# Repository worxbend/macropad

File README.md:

# macropad

A 12-key macropad on its own 4-layer PCB. Two rotary encoders, an always-on memory display,
light bars in the case sides, one USB-C port. Board, case and firmware are all generated from
code in this repository and checked against one shared file, [`board.toml`](board.toml).

It is the small, PCB-based sibling of [macropad-nyxilab](https://github.com/worxbend/macropad-nyxilab):
90 x 90 mm instead of 159 x 98 mm, and no hand wiring.

*Top: a render of the case model, not a photo. Bottom: the firmware running in its simulator, not a
recording of a device. The display in the render shows the simulator's own picture.*

> **Status: design files only. Nothing has been built.**
> No board has been ordered. No case has been printed or milled. The firmware has never run on a chip.
> Every claim below is what the design files and their automatic checks say. Read
> [Before you order](#before-you-order) first.

## Contents

1. [Status](#status)
2. [What it is](#what-it-is)
3. [Gallery](#gallery)
4. [Build one](#build-one)
5. [Stock keymap](#stock-keymap)
6. [Work on the design](#work-on-the-design)
7. [What is checked](#what-is-checked)
8. [Where things are](#where-things-are)
9. [Before you order](#before-you-order)
10. [License](#license)

## Status

Checked on 2026-11-14 by running the commands in the last column on this repository.

| Part | State | How it was checked |
|---|---|---|
| Circuit | Done. 52 nets, 75 machine-placed parts, 1 left unpopulated (C13). | `make pcb-test`: netlist self-check, 37 unit tests pass |
| Schematic | Done. Generated KiCad 9 sheet. ERC: 0 errors, 0 warnings. | `make pcb-place` (report in `pcb/.build/erc.rpt`) |
| PCB layout | **Fully routed.** 827 tracks, 164 vias, 0 unrouted pads. DRC: 0 violations, 0 unconnected, 0 differences from the schematic. | `make pcb-check` |
| Order files | Written: 11 Gerbers, 2 drill files, a BOM and a placement file each for PCBWay and JLCPCB. They agree with the board and with each other. | `make pcb-fab`, `make pcb-test` |
| Case | Done. 659 part pairs per variant, 0 clashes. Every named clearance and measurement inside its limit. Printed and milled variant. | `make test` |
| Firmware | Builds. 248 tests pass. UF2 in `firmware/dist/`. | `make test`, `make firmware` |
| Real hardware | **None.** No board, no print, no flash. | - |

One accepted DRC warning remains: the USB-C footprint differs from its library copy, because its
silkscreen is cut at the board edge. It is named in `pcb/gen/build.py` and explained in
[pcb/README.md](pcb/README.md).

A clean DRC does not make a working board. The list of things a person still has to look at is in
[Before you order](#before-you-order).

## What it is

| | |
|---|---|
| MCU | RP2354A: the Pico 2 chip (RP2350) with 2 MB flash inside the package |
| Keys | 12 x MX, HanElectricity hot-swap sockets (Kailh CPG151101S11 compatible), one GPIO per key (no matrix, no diodes) |
| Knobs | 2 x Alps EC11E18244AU with push switch, 36 clicks per turn. 3.3 kΩ pull-ups on the A and B contacts give each contact 1 mA |
| Display | nice!view (Sharp memory LCD, 160 x 68, monochrome, readable in sunlight), soldered on a 5-pin male header |
| Light | 8 x SK6812 SIDE-A side-emitting RGB LEDs on the PCB edges, behind two light bars that show as a line in the gap round the case |
| USB | One USB-C port for power, data and flashing. ESD diodes, 500 mA resettable fuse |
| Debug | Six test pads on the bottom face: SWCLK, SWDIO, GND, 5V, 3V3, 1V1. BOOT and RESET buttons reached through the case floor |
| PCB | 84 x 82.5 mm, 4 layers, 1.6 mm. Every machine-placed part is on the bottom face, next to the ground plane on In2 |
| Case | Base and top with a lap joint and a shadow gap between them, flush lens over the display, 2 light bars, 2 knobs, 2 foot strips and a centre pad that hide the screws, optional 6° tilt bar. 3D-print or CNC variant. The aluminium case is bonded to GND at one screw (H1) |
| Size | 90.0 x 90.0 x 17.5 mm, 35.5 mm from the underside to the top of the knobs. The foot strips add 1.2 mm |
| Firmware | Rust ([embassy](https://embassy.dev)). 4 layers, macros, tap-hold keys, per-layer knob functions, animated display, reactive lighting |
| Host | Shows up as a USB keyboard plus media keys. No driver, no host software |

How the pieces connect:

```mermaid
flowchart LR
    usb[USB-C] -->|5 V through fuse| reg[AP2112K 3.3 V]
    usb <-->|D+ D- through ESD diodes| mcu[RP2354A]
    reg --> mcu
    keys[12 MX keys] -->|12 GPIO| mcu
    knobs[2 encoders with push] -->|6 GPIO| mcu
    mcu -->|SPI0| lcd[nice!view]
    mcu -->|GPIO9| shift[74LVC1T45 to 5 V]
    shift --> leds[8 x SK6812 SIDE-A]
    usb -->|5 V| leds
```

More detail: [docs/hardware.md](docs/hardware.md).

## Gallery

Every picture is generated by the code in this repository. None is a photo.

### Case

The case is a 90 mm square slab with one flat top face. The printed variant has R 7.0 arc corners; the
milled variant has continuous-curvature corners. The gap between the two shells runs all round, but it
lights only along two 46.5 mm stretches, one per side. The glow colour and the brightness in the
light-line picture are guesses: no optical simulation was done. The colours are proposals.
More views, the print orientation and the design notes: [cad/README.md](cad/README.md).

### PCB

The parts on the populated board are block models with nominal heights. They show where things
are. They are not the makers' 3D models.

Schematic as [PDF](docs/images/pcb/schematic.pdf). Copper layers:
[top](docs/images/pcb/copper-top.svg), [ground](docs/images/pcb/copper-ground.svg),
[power](docs/images/pcb/copper-power.svg), [bottom](docs/images/pcb/copper-bottom.svg).
Assembly drawings: [top](docs/images/pcb/assembly-top.svg), [bottom](docs/images/pcb/assembly-bottom.svg).
Routing notes and the full check list: [pcb/README.md](pcb/README.md).

### Display and lighting

The 8 LEDs over the demo session, one row per LED. Colours are brightened for the screen.
Screens, controls and timing: [firmware/README.md](firmware/README.md).

### Drawings

The sheets are in `cad/exports/drawings/` as SVG and PDF. Dimension texts are computed from the model.
The two CNC sheets carry part numbers, revision A, one finish (bead blast and clear anodise), ISO
2768-m with the critical fits toleranced, the M2 thread callouts, the anodise masks for the case
ground at S1, a USB opening detail and, on the base, the laser-mark note. `make cad` reads every exported STEP and STL back: one closed solid per part, no
free edges, volumes within 0.1 %.

## Build one

Nobody has done this yet. The guides are written from the design files. Expect to find mistakes,
and please report them.

The plan for the first prototype, step by step with a pass test for each, is
[docs/prototype.md](docs/prototype.md): measure the parts, order the board, print coupons and a case,
bring the board up, and only then pay for a milled case.

1. **Read [Before you order](#before-you-order).** Decide whether you accept the open points.
2. **Order the board.** [docs/ordering.md](docs/ordering.md): PCBWay step by step, 5 bare boards
   with 2 assembled on the bottom face, with the files in `pcb/fab/`. JLCPCB is the alternative on
   the same page. Buy the parts the board house does not place: [docs/parts.md](docs/parts.md).
3. **Make the case.** Print the coupons first, then the case. Mill it only after a printed case
   closes on measured parts. Orientation, settings and CNC notes are in
   [cad/README.md](cad/README.md#printing).
4. **Assemble.** [docs/assembly.md](docs/assembly.md): bring up the bare board from a current-limited
   supply, run the hardware test, solder the two encoders and the display, then close the case with
   six screws.
5. **Flash.** [docs/flashing.md](docs/flashing.md): hold BOOT, plug in, copy
   `firmware/dist/macropad.uf2` to the `RP2350` drive. The same page lists what to check first when
   something does not work.

To change what the keys do: [docs/keymap.md](docs/keymap.md).

## Stock keymap

Four layers. Tap the left knob for the next layer. The display always shows the active layer's labels.

| Layer | Keys, row by row | Left knob | Right knob | Right knob press |
|---|---|---|---|---|
| MEDIA | PREV PLAY NEXT STOP / F13 F14 F15 F16 / F17 F18 F19 F20 | Volume | Screen brightness | Mute |
| EDIT | UNDO REDO CUT COPY / PASTE ALL SAVE FIND / ESC TAB-or-Shift DEL LINE | Undo, redo | Cursor left, right | Enter |
| NAV | HOME UP END PGUP / LEFT DOWN RIGHT PGDN / TAB- TAB+ BACK FWD | Up, down arrow | Previous, next tab | Enter |
| NUM | 7 8 9 BKSP / 4 5 6 ENTER / 1 2 3 0 | Volume | Minus, plus | Period |

| Gesture | Does |
|---|---|
| Hold the left knob + a top-row key | Jump to layer 1, 2, 3 or 4 |
| Hold the left knob + turn the right knob | LED brightness, 8 steps down to off |
| Hold both knobs for 1 s | Restart as a USB drive for a new firmware file |

## Work on the design

### Tools

| For | You need |
|---|---|
| Firmware | Rust (stable) with `rustup target add thumbv8m.main-none-eabihf`, Python 3.11 or newer, `make` |
| Simulator pictures | The above plus ImageMagick (`magick`) |
| Case | Python 3.12 and a virtual environment in `cad/.venv` (set-up in [cad/README.md](cad/README.md#build)). `rsvg-convert` for the PDF and PNG drawings |
| PCB | Docker. All KiCad work runs in the pinned image `kicad/kicad:9.0.9` through `pcb/kicad.sh` |

### Commands

Run `make help` for this list.

| Command | Does | Needs | Time |
|---|---|---|---|
| `make test` | Everything that can be checked without Docker or hardware | Rust, `cad/.venv` | about 3 minutes |
| `make firmware` | Tests, lints, board and HID checks, `firmware/dist/macropad.uf2` | Rust | under 1 minute |
| `make ui-images` | Redraws `docs/images/ui/` and the demo GIF from the simulator | Rust, ImageMagick | about 1 minute |
| `make cad` | Case self-test, checks, STEP/STL exports, renders, drawings | `cad/.venv` | about 3 minutes |
| `make pcb` | `pcb-place`, `pcb-check`, `pcb-fab` in order | Docker | about 2 minutes |
| `make pcb-place` | Schematic, placed and routed board, 3D models, pictures | Docker | about 1 minute |
| `make pcb-check` | KiCad design-rule check, board against schematic | Docker | seconds |
| `make pcb-fab` | Gerbers, drill files, BOM, placement list into `pcb/fab/` | Docker | seconds |
| `make pcb-test` | Netlist self-check and the PCB generator's unit tests | Python | seconds |
| `make docs-check` | Every file and picture named in a Markdown file exists | Python | seconds |

### One file drives three builds

`board.toml` holds the positions and the GPIO numbers. The PCB generator, the case model and the
firmware's board check all read it.

1. Change a position or a pin in `board.toml`.
2. Run `make pcb cad firmware`.
3. If parts or pins moved on the PCB, the routing order may need a new search:
   `pcb/kicad.sh python3 pcb/gen/build.py order` (about 10 minutes; it can fail).

Nothing in `pcb/kicad/` is drawn by hand. Hand edits are lost on the next `make pcb-place`.
Change `pcb/gen/circuit.py` or `pcb/gen/route.py` instead.

## What is checked

No check here replaces a prototype. They catch the mistakes a computer can catch.

| Area | Check | Result on 2026-11-14 |
|---|---|---|
| PCB | Netlist self-check in `circuit.py` | 52 nets, passes |
| PCB | Router, schematic-writer and order-file unit tests (15, 19, 3) | 37 pass |
| PCB | `circuit.py` pins against KiCad's own RP2354A, regulator, ESD and level-shifter symbols | match |
| PCB | Schematic ERC, every severity | 0 errors, 0 warnings |
| PCB | DRC with board-against-schematic compare | 0 violations, 0 unconnected, 0 parity issues |
| PCB | Length limits on the USB pair, crystal and regulator nets; no via on the sensitive ones | pass (D+ 14.93 mm, D- 14.08 mm) |
| PCB | Order files agree: Gerbers newer than the board, one drill hit per via, both BOMs = both placement files = circuit, C13 in none of them | 75 parts, 1 do-not-populate, pass |
| PCB | Committed order files belong to the committed board: board hash, `unrouted pads 0` | pass |
| PCB | Case ground ring at H1 on GND and bare; encoder pull-ups beside their pins; no solder paste within 0.15 mm of a via hole; the design rules reach KiCad's DRC | pass |
| Case | Self-test: the measuring checks must catch 33 known-bad and sound shapes | 33 of 33 |
| Case | Interference, every part against every other, both variants | 659 pairs each, 0 clashes |
| Case | Every part one sound solid; wall thickness, screw bosses, light bar retention and insertion, lap joint, lens seat and stiffness, key and knob travel, knob seat on its shaft, square outline, corner curvature, frame swell, foot bearing, shell seat, text strokes, USB symmetry | all inside limits |
| Case | CNC: 3 mm tool reaches every pocket within 3 diameters, no sharp internal corner, no undercut beyond the USB opening's rounds | pass |
| Case | Exports read back: 11 STEP files, each part file one closed valid solid and the assembly 81, 0 free edges, volume within 0.1 % of the model and of its STL; no sliver faces in the CNC parts; 9 print coupons, each one watertight body | 11 of 11 STEP, 9 of 9 coupons |
| Case | Print: layer-by-layer bridge and overhang check for every printed part, faces on the 0.2 mm layer grid, show faces of the top at 45° or less, engraving on the bed 0.7 mm wide | pass |
| Firmware | Unit tests: `core` 192, `sim` 38, `uf2` 18 | 248 pass |
| Firmware | `tools/check_pins.py`: GPIOs, knob type, knob debounce longer than the encoder's 3 ms chatter, key grid, LED and simulator positions against `board.toml` | match |
| Firmware | `tools/check_hid.py`: the USB report descriptors, parsed as a host would | match |
| Firmware | UF2 converter refuses an image the chip could not boot | current image passes |
| Docs | `make docs-check`: files and pictures named in Markdown exist | pass |

CI ([`.github/workflows/ci.yml`](.github/workflows/ci.yml)) runs the checks that need neither Docker
nor a long case build: `make pcb-test`, `make docs-check` and the firmware tests with both board
checks. The workflow has not run on GitHub yet.

## Where things are

| Path | What |
|---|---|
| [`board.toml`](board.toml) | Positions and GPIOs. The single source of truth for PCB, case and firmware. |
| [`pcb/`](pcb/README.md) | The board. `gen/` is the generator (`circuit.py` is the circuit), `kicad/` the generated KiCad 9 project, `fab/` the order files, `lib/` footprints and block models. |
| [`cad/`](cad/README.md) | Parametric case (build123d). `macropad_case/` is the model and its checks, `exports/` holds STEP, STL, drawings and `checks.json`. |
| [`firmware/`](firmware/README.md) | Rust workspace: `core` logic, `fw` binary, `sim` simulator, `uf2` converter. `dist/macropad.uf2` is the built image. [`KEYMAP.md`](firmware/KEYMAP.md) is the keymap reference. |
| `tools/` | `check_pins.py` and `check_hid.py`: firmware against `board.toml` and against the HID rules. |
| [`docs/hardware.md`](docs/hardware.md) | Circuit in words, pin map, layer stack, test pads, mechanical stack. |
| [`docs/parts.md`](docs/parts.md) | Every part, its JLCPCB number, what to buy elsewhere, substitutions, a shopping list for the prototype. |
| [`docs/prototype.md`](docs/prototype.md) | The staged plan for the first prototype, with a pass test per step. |
| [`docs/ordering.md`](docs/ordering.md) | Ordering the assembled board from PCBWay, step by step; JLCPCB as the alternative. |
| [`docs/assembly.md`](docs/assembly.md) | Bring-up of a bare board, soldering, case assembly. |
| [`docs/flashing.md`](docs/flashing.md) | First flash, updates, troubleshooting. |
| [`docs/keymap.md`](docs/keymap.md) | Changing what the keys, knobs and lights do. |
| `docs/images/` | Generated pictures: `cad/`, `pcb/`, `ui/`. |

## Before you order

These are open. None is hidden by a green check.

**Electrical**

- **Crystal.** Raspberry Pi's reference part, the Abracon ABM8-272-T3, with the reference 15 pF
  capacitors and 1 kΩ. Not measured. If USB does not enumerate, look here first.
  See [docs/parts.md](docs/parts.md).
- **USB pair.** Two short tracks, 14.9 and 14.1 mm, not a tuned differential pair. No impedance was
  calculated. Normal for full-speed USB over this length; nobody measured it.
- **Regulator inductor dot.** The two papers disagree. Raspberry Pi's datasheet and reference
  layout put the dot on +1V1; Abracon's drawing labels the dot "+". The board follows Raspberry Pi:
  dot on the +1V1 pad, next to the silkscreen dot. Mounting on the bottom face changes nothing here:
  the regulator reads as Raspberry Pi's Fig. 26 seen from the bottom. Not verified on a part.
- **Placement rotations.** `pcb/fab/centroid-pcbway.csv` and `pcb/fab/cpl-jlcpcb.csv` carry KiCad's
  angles, also for the bottom-side parts. Whether the assembler wants those or (180 - r) is not
  settled. Check every part in their placement photos or preview before you pay;
  [docs/ordering.md](docs/ordering.md) has the checklist.
- **Suspend current.** The 8 LEDs draw about 4.8 mA even when dark, over the 2.5 mA a suspended USB
  device may draw, and the MCU keeps running too. Accepted for the prototype. The fix is a load
  switch on the LED supply: a board change.
- **C13 is left unpopulated.** Its 4.7 µF would double the 1.1 V regulator's output capacitor.
  The footprint stays; its two pads get solder paste and no part.
- **Hot-swap socket footprint.** The board uses HanElectricity's CPG151101S11-2. The footprint was
  drawn from Kailh's CPG151101S11 dimensions. HanElectricity's drawing gives the same main sizes, but
  nobody has checked the footprint against it pad by pad.

Settled since the last revision: the nice!view header order (MOSI, SCK, VCC, GND, CS) matches the
pinout on nicekeyboards.com, and the SK6812 SIDE-A pad order matches the OPSCO datasheet by function.
Both stay tagged `MEASURE` until someone checks a real module and LED.

**Mechanical**

- **`MEASURE` dimensions.** The nice!view's pixel window, its height on a plain male header (glass 4.4 mm
  above the PCB) and its header position, and the encoder heights (shaft end 24.5 mm, from the Alps
  drawing), come from drawings and community footprints, not from a caliper. The full table is in
  [cad/README.md](cad/README.md#assumptions-to-measure). Measure before you order the board:
  `display.header_x` moves J2 on the PCB.
- **Fits are guesses.** Lap joint 0.2 mm, deepest unsupported ledge 1.5 mm, sag of a printed bridge
  0.2 mm, printed screw holes 0.15 mm small, lens 1.0 mm cover glass on 0.13 mm tape. Print the nine
  coupons in `cad/exports/print/coupons/`, then one case, and measure before paying for machining.
- **The light line is a guess.** The LEDs shine into a bar that shows only through a 1.4 mm slit in the
  gap. How bright and how even that is has not been simulated or tried.
- **The top prints standing on its side wall**, 10.6 times taller than its footprint is wide. Tipping
  and warping are not modelled.

**Firmware**

- **Display orientation, knob direction, LED colour order** are one-line settings and are guesses
  until a board exists. [docs/flashing.md](docs/flashing.md) says where each one is.
- **USB IDs** are the pid.codes test pair `1209:0001`. Get your own before you give boards to others.
- Settings are not stored: brightness and layer reset at power-on.

**Review**

- The schematic and the layout are generated and machine-checked. No engineer has reviewed them.

## License

No license file yet. Until one is added, nobody else has the right to reuse this.
The side-LED footprint comes from another project under the MIT License; see `pcb/lib/SOURCES.txt`.

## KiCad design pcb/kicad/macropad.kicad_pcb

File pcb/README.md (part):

# PCB

The board is generated. Nothing in `pcb/kicad/` is drawn by hand: `make pcb-place` writes the
schematic, the placed and routed board, and the pictures in `docs/images/pcb/` from two inputs,
`board.toml` (positions, GPIOs) and `pcb/gen/circuit.py` (parts and nets).

**Not built.** No board has been ordered, assembled or powered. Everything below is what the design
files say and what the automatic checks confirm, nothing more.

Bare-board renders (KiCad 9). Left: top face with the keys, knobs and display header. Right: bottom
face with every machine-placed part.

The same board with its parts. The parts are block models: boxes and cylinders that `gen/models.py`
draws from each footprint's outline, with nominal heights. They show where things are and which face
they are on. They are not the manufacturers' models. Straight-on views:
[top](../docs/images/pcb/assembled-top.png), [bottom](../docs/images/pcb/assembled-bottom.png).

## Commands

| Command | What it does |
|---|---|
| `make pcb-place` | Place, route, pour, write the schematic, check it, export the pictures. About 2 minutes. Fails when a pad is left unrouted, after writing `routing.txt`. |
| `make pcb-check` | KiCad design-rule check of the routed board. Fails on any error or unconnected item. |
| `make pcb-fab` | Gerbers, drill files, JLCPCB and PCBWay BOMs and placement files into `pcb/fab/`, then a check that they agree. |
| `make pcb-test` | `python3 -m unittest discover -s pcb/gen -p 'test_*.py'`: router, schematic-writer and order-file tests (37). Plain Python, no KiCad needed. CI runs it. |
| `pcb/kicad.sh python3 pcb/gen/build.py order` | Search for a routing order again. Needed after moving parts or pins. About 10 minutes. |

All KiCad work runs in the pinned container `kicad/kicad:9.0.9` through `pcb/kicad.sh`.

## Files

| Path | What |
|---|---|
| `gen/circuit.py` | The circuit: every part, its JLCPCB number, position, rotation, nets and do-not-populate mark. Pure Python. |
| `gen/layout.py` | Footprints, board outline, planes, design rules (also written into `kicad/macropad.kicad_pro`), the MCU footprint's paste windows, placement self-checks. |
| `gen/router.py` | Two-layer grid router. Pure Python, tested in `gen/test_router.py`. |
| `gen/route.py` | The routing plan: what is routed in which order, and the hand-placed vias. |
| `gen/route_order.txt` | MCU nets that are routed before the others. Written by `build.py order`. |
| `gen/silk.py` | Silkscreen text. |
| `gen/models.py` | Block 3D models of the parts, written to `lib/3d/`. |
| `gen/schematic.py` | Writes the KiCad schematic from `circuit.py`, with KiCad's library symbols. |
| `gen/sheet_layout.py` | Where each part sits on the schematic sheet and which wires are drawn. Data only. |
| `gen/symlib.py`, `gen/sexpr.py` | Read KiCad symbol libraries; draw the two symbols KiCad has none for. |
| `gen/test_schematic.py` | Tests of the schematic writer. |
| `gen/test_order_files.py` | The committed board and order files belong together: no unrouted pad, Gerbers not older than the board, board hash as `make pcb-fab` recorded it. |
| `gen/fab.py` | JLCPCB and PCBWay BOMs, JLCPCB placement list, PCBWay centroid file, and their checks. |
| `kicad/` | Generated KiCad 9 project: board, schematic, symbol library, library tables. |
| `routing.txt` | Generated report: track length and via count per net. |
| `netlist.txt` | Generated netlist: `python3 pcb/gen/circuit.py > pcb/netlist.txt`. |
| `lib/` | The project footprints and where they come from (`lib/SOURCES.txt`). The MCU footprint with windowed exposed-pad paste is generated by `gen/layout.py`. `lib/3d/` holds the generated block models. |
| `fab/` | Generated order files: `macropad-gerbers.zip`, `bom-jlcpcb.csv`, `cpl-jlcpcb.csv`, `bom-pcbway.csv`, `centroid-pcbway.csv`, and `board-sha256.txt` (the board they were made from). |

## Schematic

`kicad/macropad.kicad_sch` opens in KiCad 9. One A3 sheet, thirteen blocks.
[PDF](../docs/images/pcb/schematic.pdf), [SVG](../docs/images/pcb/schematic.svg).

It is a drawing of `circuit.py`, not a second source of truth:

- **Symbols come from KiCad's own libraries** (`Device:R`, `MCU_RaspberryPi:RP2354A`,
  `Regulator_Linear:AP2112K-3.3`, `Power_Protection:USBLC6-2SC6`, `Logic_LevelTranslator:SN74LVC1T45DBV`,
  `Connector:USB_C_Receptacle_USB2.0_16P` and so on). Pin numbers, pin names and pin types are
  therefore KiCad's, not typed here. Two parts have no KiCad symbol and are drawn as boxes: the
  side LED and the display header.
- **`sheet_layout.py` places the parts and lists the drawn wires.** Every other pin gets its supply
  symbol or its net label by rule. A drawn wire names its net, and the build refuses a wire that
  touches a pin of another net.

Checks on every `make pcb-place`:

1. `circuit.py` against KiCad's RP2354A symbol: each GPIO on its pin, each supply pin on its rail,
   the five pins of the flash inside the package open. Each chip's footprint against the footprint
   KiCad's symbol names.
2. `kicad-cli sch erc` at every severity: no error, no warning. That includes KiCad comparing each
   symbol on the sheet with its library.
3. KiCad exports the schematic's netlist; every pin's net is compared with `circuit.py`.
4. `kicad-cli pcb drc --schematic-parity`: every footprint, value and pad net on the board equals
   the schematic.

What this does not prove: KiCad's RP2354A symbol is itself someone's reading of the datasheet. It
is an independent one, and it agrees with `circuit.py` on all 61 pins. The SK6812 SIDE-A and
nice!view pin orders are still `MEASURE` items; no library covers them.

## Layers

| Layer | Use |
|---|---|
| F.Cu | Signals that cross the chip area, ground pour, the bare case ground ring at H1 |
| In1.Cu | 5 V plane. Inside it a 3.3 V island under the MCU, the display header and the USB pair, with a tongue out to the left encoder's pull-ups. Inside that a 1.1 V island under the chip |
| In2.Cu | Ground plane, unbroken except under the regulator inductor and the VREG_LX track |
| B.Cu | All machine-placed parts, most signals (1067 of 1308 mm of track), ground pour |

Drawings of each layer: [top](../docs/images/pcb/copper-top.svg),
[ground](../docs/images/pcb/copper-ground.svg), [power](../docs/images/pcb/copper-power.svg),
[bottom](../docs/images/pcb/copper-bottom.svg). Assembly drawings:
[top](../docs/images/pcb/assembly-top.svg), [bottom, mirrored](../docs/images/pcb/assembly-bottom.svg).

## Design rules

| Rule | Value | Note |
|---|---|---|
| Track width | 0.15 mm signals, 0.3 mm supply where it fits | |
| Clearance | 0.15 mm | The router keeps 0.17 mm to allow for its 0.1 mm grid |
| Via | 0.6 mm pad, 0.3 mm drill | No vias in pads, except four in the MCU's exposed pad. Every via is tented on the top face; on the bottom face all are tented except those four, which sit in the pad's mask opening and get no paste |
| Copper to board edge | 0.3 mm | |
| Copper to hole | 0.2 mm | Hole to hole 0.25 mm |
| Paste to via hole | 0.15 mm | No solder-paste aperture comes closer than this to a drilled via hole |

These are inside JLCPCB's published 4-layer limits as the previous author recorded them in
`layout.py`. PCBWay's capability page (read 2026-11-14) gives 0.1 mm track and space, 0.15 mm
minimum drill and 0.15 mm minimum via annular ring for its standard boards; the 0.6 / 0.3 mm via
has exactly 0.15 mm. Check them against the board house's page on the day you order.

KiCad 9 keeps the design rules in `kicad/macropad.kicad_pro`, not in the board file, and saving the
board from Python does not write that file. Until this change the file was the one written on
12 November and never touched by the build; its values happened to match. Now `make pcb-place`
writes `layout.DRC_RULES` and the default net class into it, and proves that `kicad-cli pcb drc`
reads them: a copy of the board with a project file that asks for 0.2 mm minimum track width must
fail on track width (199 findings on this board).

**Exposed-pad paste.** The MCU's exposed pad carries four 0.3 mm ground vias. KiCad's stock QFN-60
prints paste over them, so solder would wick into the holes. The board uses a project copy of the
stock footprint (`lib/macropad.pretty/QFN-60-1EP_7x7mm_P0.4mm_EP3.4x3.4mm_ViaWindows`, written by
`layout.py`) with the copper unchanged and the paste as nine windows: a 1.1 mm square in the middle,
four 0.95 x 1.1 mm arms between the vias and four 0.33 mm corner squares. They cover 50 % of the
pad and stay 0.15 mm clear of each via's 0.6 mm copper ring (0.3 mm from the hole). The vias are
tented on the top face. Nobody has checked the result with X-ray or a cut board; the corner squares
are small for a 0.12 mm stencil (area ratio about 0.69; the stencil thickness is a guess, ask the
board house).

## How the routing works

There is no autorouter program. `router.py` is a small grid router and `route.py` tells it what to
do, in this order:

1. **Four ground vias** in the MCU's exposed pad, between its paste windows.
2. **1.1 V regulator**, in Raspberry Pi's RP2350A Minimal pattern (RP2350 datasheet 6.3.8), mirrored
   for the bottom face. CIN (C11) sits across VREG_VIN (pin 49) and PGND (pin 47), COUT (C12) right
   behind it; their ground pads are joined and share two hand-placed vias. VREG_LX runs from pin 48
   between the pads of both capacitors to the inductor beyond them. VREG_FB runs from pin 50 to
   COUT. A 0.3 mm link takes the output from the inductor's +1V1 pad over the chip on the top layer
   into the 1.1 V island. Rule areas keep copper off the top and both inner layers under the
   inductor and the VREG_LX node, and keep the bottom ground pour out from between the inductor's
   pads. The VREG_LX rule areas are drawn after routing, round pin 48 and each routed VREG_LX segment
   with 0.2 mm to spare, so they follow the track wherever the router put it. Then USB D+ and D-, which squeeze past the regulator to their series resistors.
3. **MCU supply pins.** Each pin runs to its own 100 nF capacitor. The supply via sits between the
   pin and the capacitor, the ground via behind the capacitor, all on one line pointing away from
   the chip. These vias are placed by hand-computed geometry (`circuit.py`: `DECOUPLING_DISTANCE`,
   `SUPPLY_VIA_DISTANCE`, `GROUND_VIA_DISTANCE`), so they stay out of the lanes the neighbouring
   signal pins need.
4. **Crystal ground vias**, then **RUN**, then **SWCLK and SWDIO** out of the chip.
5. **Sensitive nets**, while the board is still empty: the USB lines from the connector, the crystal
   nets, VREG_AVDD. Then QSPI_SS, BOOT and VBUS.
6. **One via to the plane** for every remaining supply and ground pad.
7. **MCU signals**, one pin at a time: first a track out of the 16 mm square around the chip, then
   the rest of the net. Pins next to a capacitor go first. `route_order.txt` moves some nets to the
   front.
8. **Everything else**, shortest net first.

The router has no rip-up. When a net ends up walled in, `build.py order` routes the whole board
again with that net moved to the front, until every net connects. The order it finds is stored in
`route_order.txt`, so `make pcb-place` is one deterministic pass.

## Checks

| Check | Where | Fails the build |
|---|---|---|
| Every net has at least two pads | `circuit.py` | yes |
| Flips and rotations: MCU pins, hot-swap sockets, USB mouth, LED direction, capacitor orientation, crystal near XIN, fiducials on the assembly face | `layout.py:check_placement` | yes |
| Router: clearance to pads, tracks, vias, holes and the edge; vias; fan-out; escapes; determinism (15 tests) | `test_router.py` | yes, in `make pcb-test` and CI |
| Hand-placed vias have room | `router.py:add_via` | yes |
| Every net connects through tracks, vias and inner planes alone, before the outer ground pours are added | `build.py` | yes |
| Length limits: VREG_LX, USB_DM, USB_DP, XIN, XOUT, VREG_AVDD, VREG_FB to COUT; USB pair mismatch under 2 mm; no via on VREG_LX, on USB D+ from connector to chip, or on D- after its resistor; VREG_AVDD at least 0.75 mm from VREG_LX | `route.py:check_sensitive_lengths` | yes |
| No via and no top-layer track under the regulator inductor or the VREG_LX track | `route.py:check_regulator_keepout` | yes |
| No filled pour on the top or inner layers under the VREG_LX tracks, pin 48 or the inductor's pads, read back from the filled board | `route.py:check_no_pour_under_regulator` | yes |
| L1's polarity dot on B.SilkS and B.Fab sits at its +1V1 pad | `layout.py:check_placement` | yes |
| Encoder pull-ups R10-R13: on the bottom face, within 3 mm of their encoder pin, signal pad toward the pin | `layout.py:check_placement` | yes |
| Case ground ring at H1: on GND, at `mounting.ground_bond_hole`, `mounting.ground_bond_pad_diameter` wide, 2.2 mm hole, bare on the top face; no pad, track or via of another net within 0.15 mm | `layout.py:check_ground_bond`, after placement and after routing | yes |
| The MCU footprint's copy has exactly the stock footprint's copper pads; its paste windows stay inside the exposed pad, 0.15 mm clear of each via's copper ring, and cover 50 to 70 % of the pad | `layout.py:check_derived_footprints`, `check_paste_windows` | yes |
| Board-wide: no paste aperture within 0.15 mm of a via hole; every via tented on the top face | `layout.py:check_paste_clear_of_vias` | yes |
| `kicad-cli pcb drc` reads the rules from `macropad.kicad_pro`: a stricter project file must make it fail | `build.py:_check_rules_reach_drc` | yes |
| No pad left unrouted; `routing.txt` is written first | `build.py:place` | yes |
| Silkscreen: every visible text, footprint references included, at least 1.0 mm high with a 0.15 mm stroke; every stroked line at least 0.15 mm wide (the generator widens the stock footprints' 0.12 mm lines) | `silk.py:check_minimums` | yes |
| Every real part has a JLCPCB number, a manufacturer and a manufacturer part number | `circuit.py:check_sourcing` | yes, in `make pcb-test` |
| KiCad DRC at every severity: no warning either (loose track end, silkscreen over a pad or the edge). One named exception: J1 differs from its library copy, because its silkscreen is cut at the board edge | `build.py:_check_no_warnings` | yes |
| Every real part has a 3D model; no bottom-side model is taller than the gap to the case floor | `layout.py:write_models` | yes |
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
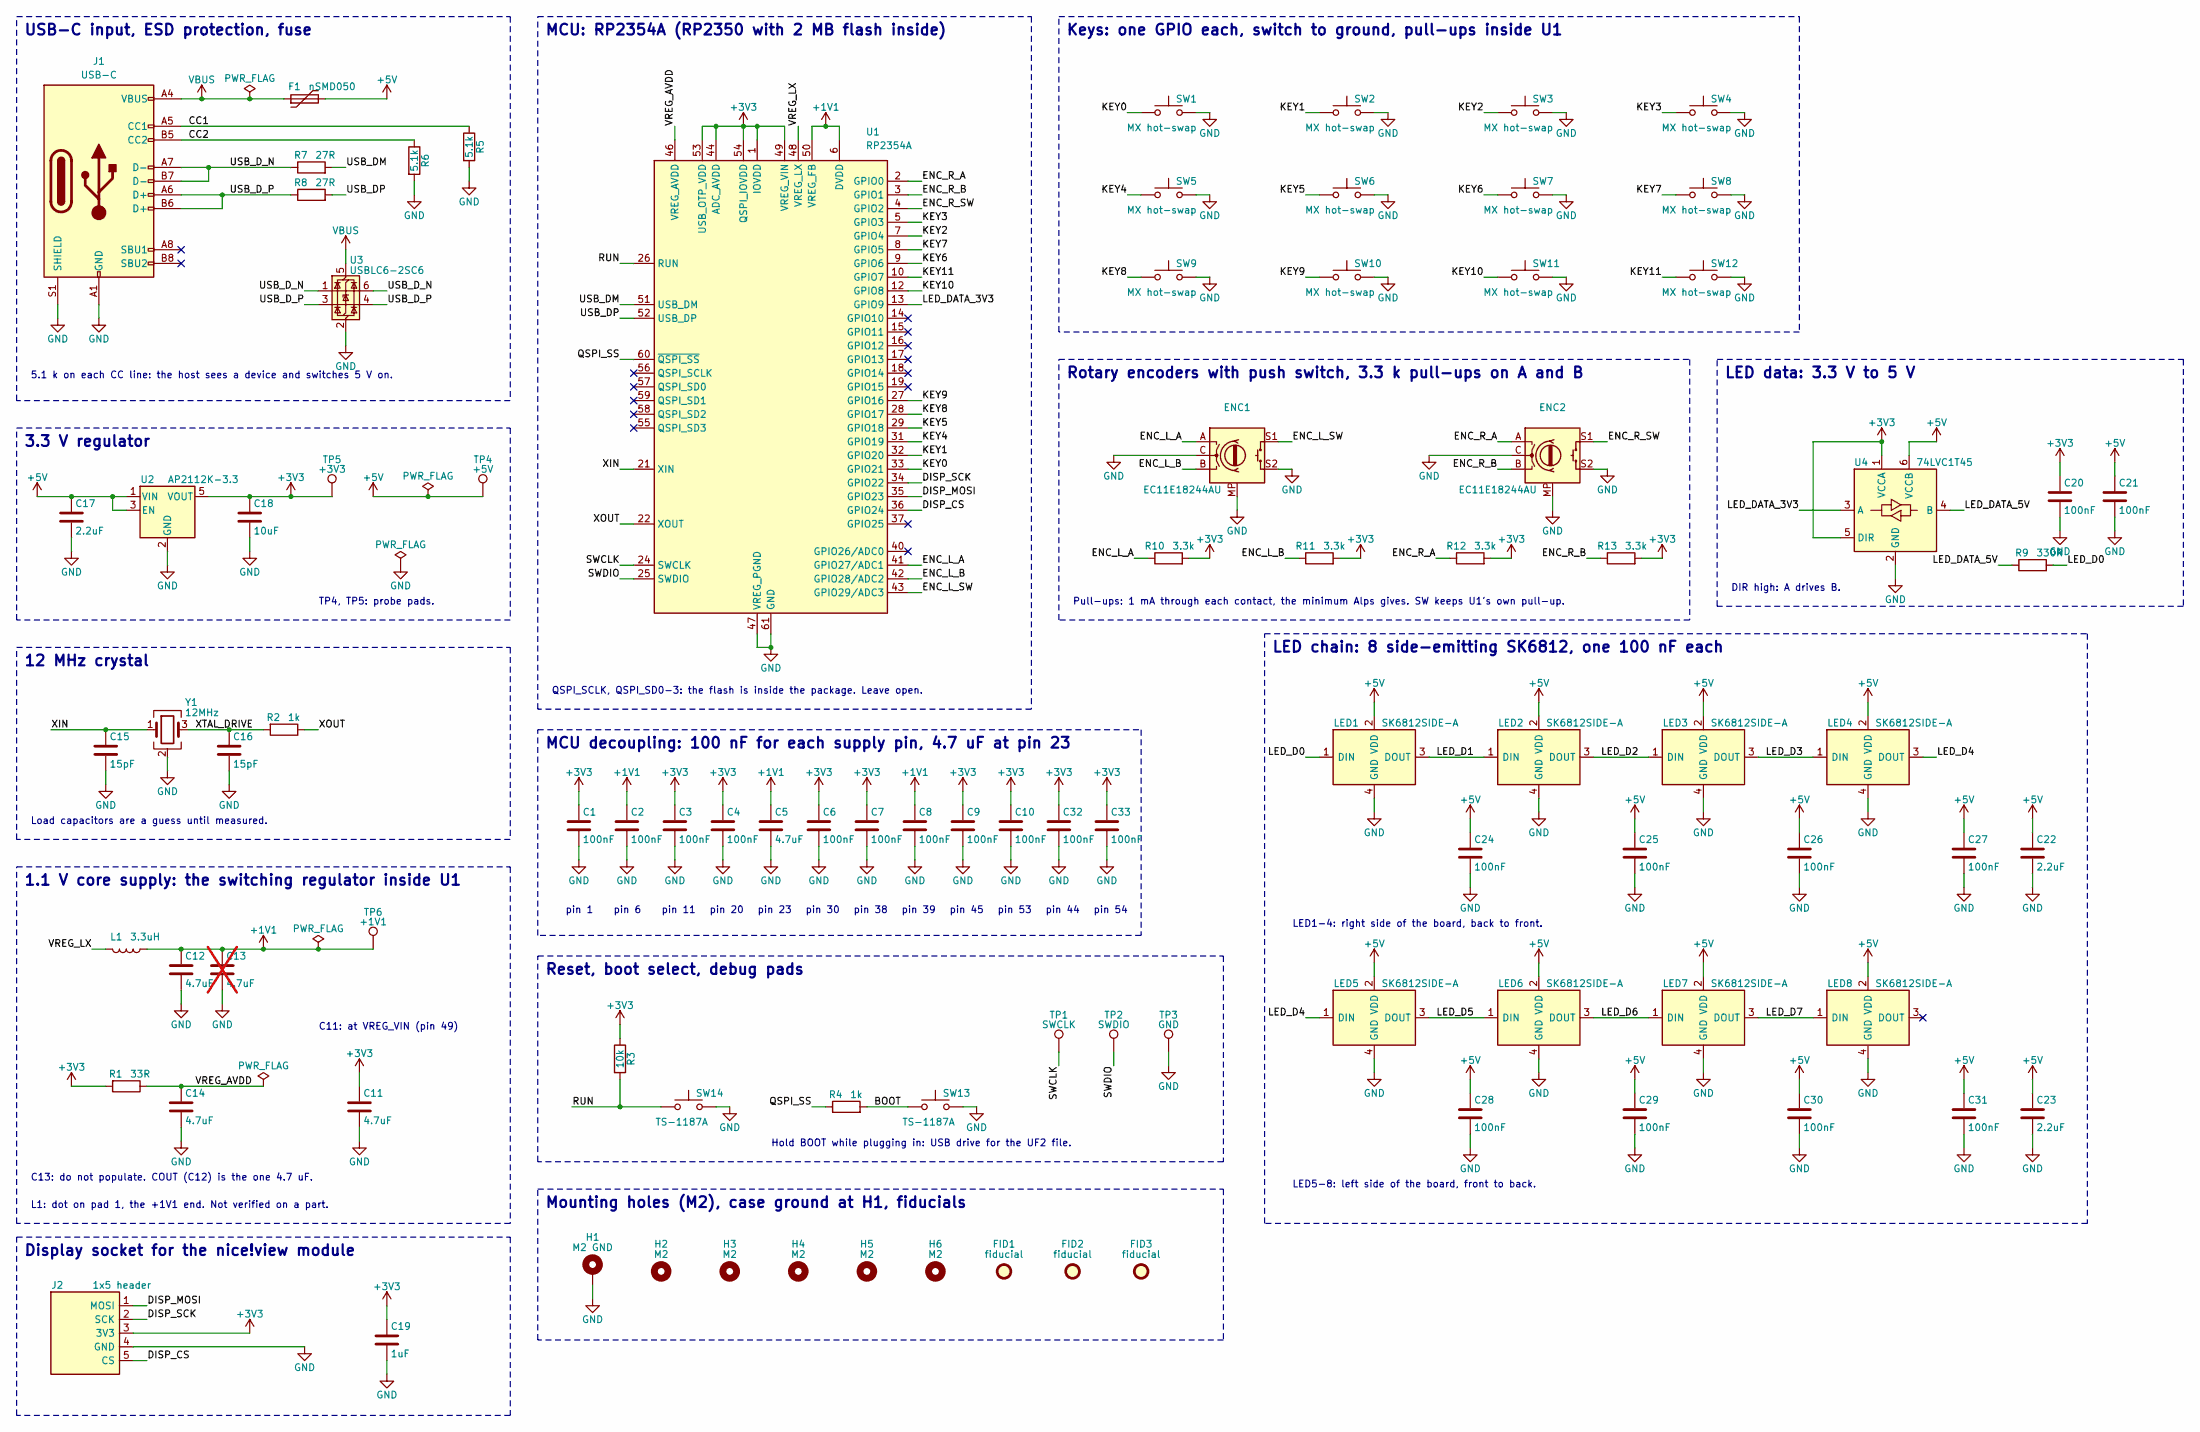
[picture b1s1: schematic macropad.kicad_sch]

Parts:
C1, C2, C3, C4, C6, C7, C8, C9, C10, C20, C21, C24, C25, C26, C27, C28, C29, C30, C31, C32, C33: 100nF; C_0402_1005Metric; LCSC C1525
C5: 4.7uF; C_0402_1005Metric; LCSC C23733
C11, C12, C14: 4.7uF; C_0402_1005Metric_Wide; LCSC C23733
C13: 4.7uF; C_0402_1005Metric_Wide; LCSC C23733; not fitted
C15, C16: 15pF; C_0402_1005Metric; LCSC C1548
C17, C22, C23: 2.2uF; C_0603_1608Metric; LCSC C23630
C18: 10uF; C_0603_1608Metric; LCSC C19702
C19: 1uF; C_0402_1005Metric; LCSC C52923
ENC1, ENC2: EC11E18244AU; RotaryEncoder_Alps_EC11E-Switch_Vertical_H20mm; LCSC C202365
F1: nSMD050; Fuse_1206_3216Metric; LCSC C69688
FID1, FID2, FID3: fiducial; Fiducial_1mm_Mask2mm
H1: M2 GND; Hole_M2_Ground
H2, H3, H4, H5, H6: M2; Hole_M2
J1: USB-C; USB_C_Receptacle_HRO_TYPE-C-31-M-12; LCSC C165948
J2: 1x5 header; PinSocket_1x05_P2.54mm_Vertical; LCSC C2337
L1: 3.3uH; L_Abracon_AOTA-B201610; LCSC C42411119
LED1, LED2, LED3, LED4, LED5, LED6, LED7, LED8: SK6812SIDE-A; SK6812-side-a; LCSC C5378721
R1: 33R; R_0402_1005Metric; LCSC C25105
R2, R4: 1k; R_0402_1005Metric; LCSC C11702
R3: 10k; R_0402_1005Metric; LCSC C25744
R5, R6: 5.1k; R_0402_1005Metric; LCSC C25905
R7, R8: 27R; R_0402_1005Metric; LCSC C25100
R9: 330R; R_0402_1005Metric; LCSC C25104
R10, R11, R12, R13: 3.3k; R_0402_1005Metric; LCSC C25890
SW1, SW2, SW3, SW4, SW5, SW6, SW7, SW8, SW9, SW10, SW11, SW12: MX hot-swap; MX_Hotswap; LCSC C49352235
SW13, SW14: TS-1187A; SW_Push_1P1T_XKB_TS-1187A; LCSC C318884
TP1: SWCLK; TestPoint_Pad_D1.0mm
TP2: SWDIO; TestPoint_Pad_D1.0mm
TP3: GND; TestPoint_Pad_D1.0mm
TP4: +5V; TestPoint_Pad_D1.0mm
TP5: +3V3; TestPoint_Pad_D1.0mm
TP6: +1V1; TestPoint_Pad_D1.0mm
U1: RP2354A; QFN-60-1EP_7x7mm_P0.4mm_EP3.4x3.4mm_ViaWindows; LCSC C41378174
U2: AP2112K-3.3; SOT-23-5; LCSC C51118
U3: USBLC6-2SC6; SOT-23-6; LCSC C7519
U4: 74LVC1T45; SOT-23-6; LCSC C168856
Y1: 12MHz; Crystal_SMD_3225-4Pin_3.2x2.5mm; LCSC C20625731

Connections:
+1V1: C2.1, C5.1, C8.1, C12.1, C13.1, L1.1, TP6.1, U1.6 (DVDD), U1.23 (DVDD), U1.39 (DVDD), U1.50 (VREG_FB)
+3V3: C1.1, C3.1, C4.1, C6.1, C7.1, C9.1, C10.1, C11.1, C18.1, C19.1, C20.1, C32.1, C33.1, J2.3 (3V3), R1.2, R3.1, R10.2, R11.2, R12.2, R13.2, TP5.1, U1.1 (IOVDD), U1.11 (IOVDD), U1.20 (IOVDD), U1.30 (IOVDD), U1.38 (IOVDD), U1.44 (ADC_AVDD), U1.45 (IOVDD), U1.49 (VREG_VIN), U1.53 (USB_OTP_VDD), U1.54 (QSPI_IOVDD), U2.5 (VOUT), U4.1 (VCCA), U4.5 (DIR)
+5V: C17.1, C21.1, C22.1, C23.1, C24.1, C25.1, C26.1, C27.1, C28.1, C29.1, C30.1, C31.1, F1.2, LED1.2 (VDD), LED2.2 (VDD), LED3.2 (VDD), LED4.2 (VDD), LED5.2 (VDD), LED6.2 (VDD), LED7.2 (VDD), LED8.2 (VDD), TP4.1, U2.1 (VIN), U2.3 (EN), U4.6 (VCCB)
/BOOT: R4.2, SW13.1
/CC1: J1.A5 (CC1), R5.1
/CC2: J1.B5 (CC2), R6.1
/DISP_CS: J2.5 (CS), U1.36 (GPIO24)
/DISP_MOSI: J2.1 (MOSI), U1.35 (GPIO23)
/DISP_SCK: J2.2 (SCK), U1.34 (GPIO22)
/ENC_L_A: ENC1.A, R10.1, U1.41 (GPIO27/ADC1)
/ENC_L_B: ENC1.B, R11.1, U1.42 (GPIO28/ADC2)
/ENC_L_SW: ENC1.S1, U1.43 (GPIO29/ADC3)
/ENC_R_A: ENC2.A, R12.1, U1.2 (GPIO0)
/ENC_R_B: ENC2.B, R13.1, U1.3 (GPIO1)
/ENC_R_SW: ENC2.S1, U1.4 (GPIO2)
/KEY0: SW1.1, U1.33 (GPIO21)
/KEY1: SW2.1, U1.32 (GPIO20)
/KEY2: SW3.1, U1.7 (GPIO4)
/KEY3: SW4.1, U1.5 (GPIO3)
/KEY4: SW5.1, U1.31 (GPIO19)
/KEY5: SW6.1, U1.29 (GPIO18)
/KEY6: SW7.1, U1.9 (GPIO6)
/KEY7: SW8.1, U1.8 (GPIO5)
/KEY8: SW9.1, U1.28 (GPIO17)
/KEY9: SW10.1, U1.27 (GPIO16)
/KEY10: SW11.1, U1.12 (GPIO8)
/KEY11: SW12.1, U1.10 (GPIO7)
/LED_D0: LED1.1 (DIN), R9.2
/LED_D1: LED1.3 (DOUT), LED2.1 (DIN)
/LED_D2: LED2.3 (DOUT), LED3.1 (DIN)
/LED_D3: LED3.3 (DOUT), LED4.1 (DIN)
/LED_D4: LED4.3 (DOUT), LED5.1 (DIN)
/LED_D5: LED5.3 (DOUT), LED6.1 (DIN)
/LED_D6: LED6.3 (DOUT), LED7.1 (DIN)
/LED_D7: LED7.3 (DOUT), LED8.1 (DIN)
/LED_DATA_3V3: U1.13 (GPIO9), U4.3 (A)
/LED_DATA_5V: R9.1, U4.4 (B)
/QSPI_SS: R4.1, U1.60 (~QSPI_SS)
/RUN: R3.2, SW14.1, U1.26 (RUN)
/SWCLK: TP1.1, U1.24 (SWCLK)
/SWDIO: TP2.1, U1.25 (SWDIO)
/USB_DM: R7.2, U1.51 (USB_DM)
/USB_DP: R8.2, U1.52 (USB_DP)
/USB_D_N: J1.A7 (D-), J1.B7 (D-), R7.1, U3.1 (I/O1), U3.6 (I/O1)
/USB_D_P: J1.A6 (D+), J1.B6 (D+), R8.1, U3.3 (I/O2), U3.4 (I/O2)
/VREG_AVDD: C14.1, R1.1, U1.46 (VREG_AVDD)
/VREG_LX: L1.2, U1.48 (VREG_LX)
/XIN: C15.1, U1.21 (XIN), Y1.1
/XOUT: R2.1, U1.22 (XOUT)
/XTAL_DRIVE: C16.1, R2.2, Y1.3
GND: C1.2, C2.2, C3.2, C4.2, C5.2, C6.2, C7.2, C8.2, C9.2, C10.2, C11.2, C12.2, C13.2, C14.2, C15.2, C16.2, C17.2, C18.2, C19.2, C20.2, C21.2, C22.2, C23.2, C24.2, C25.2, C26.2, C27.2, C28.2, C29.2, C30.2, C31.2, C32.2, C33.2, ENC1.C, ENC1.MP, ENC1.S2, ENC2.C, ENC2.MP, ENC2.S2, H1.1, J1.A1 (GND), J1.A12 (GND), J1.B1 (GND), J1.B12 (GND), J1.S1 (SHIELD), J2.4 (GND), LED1.4 (GND), LED2.4 (GND), LED3.4 (GND), LED4.4 (GND), LED5.4 (GND), LED6.4 (GND), LED7.4 (GND), LED8.4 (GND), R5.2, R6.2, SW1.2, SW2.2, SW3.2, SW4.2, SW5.2, SW6.2, SW7.2, SW8.2, SW9.2, SW10.2, SW11.2, SW12.2, SW13.2, SW14.2, TP3.1, U1.47 (VREG_PGND), U1.61 (GND), U2.2 (GND), U3.2 (GND), U4.2 (GND), Y1.2 (G), Y1.4 (G)
VBUS: F1.1, J1.A4 (VBUS), J1.A9 (VBUS), J1.B4 (VBUS), J1.B9 (VBUS), U3.5 (VBUS)

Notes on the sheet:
USB-C input, ESD protection, fuse
5.1 k on each CC line: the host sees a device and switches 5 V on.
3.3 V regulator
TP4, TP5: probe pads.
12 MHz crystal
Load capacitors are a guess until measured.
1.1 V core supply: the switching regulator inside U1
C11: at VREG_VIN (pin 49)
C13: do not populate. COUT (C12) is the one 4.7 uF.
L1: dot on pad 1, the +1V1 end. Not verified on a part.
Display socket for the nice!view module
MCU: RP2354A (RP2350 with 2 MB flash inside)
QSPI_SCLK, QSPI_SD0-3: the flash is inside the package. Leave open.
MCU decoupling: 100 nF for each supply pin, 4.7 uF at pin 23
pin 1
pin 6
pin 11
pin 20
pin 23
pin 30
pin 38
pin 39
pin 45
pin 53
pin 44
pin 54
Reset, boot select, debug pads
Hold BOOT while plugging in: USB drive for the UF2 file.
Mounting holes (M2), case ground at H1, fiducials
Keys: one GPIO each, switch to ground, pull-ups inside U1
Rotary encoders with push switch, 3.3 k pull-ups on A and B
Pull-ups: 1 mA through each contact, the minimum Alps gives. SW keeps U1's own pull-up.
LED data: 3.3 V to 5 V
DIR high: A drives B.
LED chain: 8 side-emitting SK6812, one 100 nF each
LED1-4: right side of the board, back to front.
LED5-8: left side of the board, front to back.

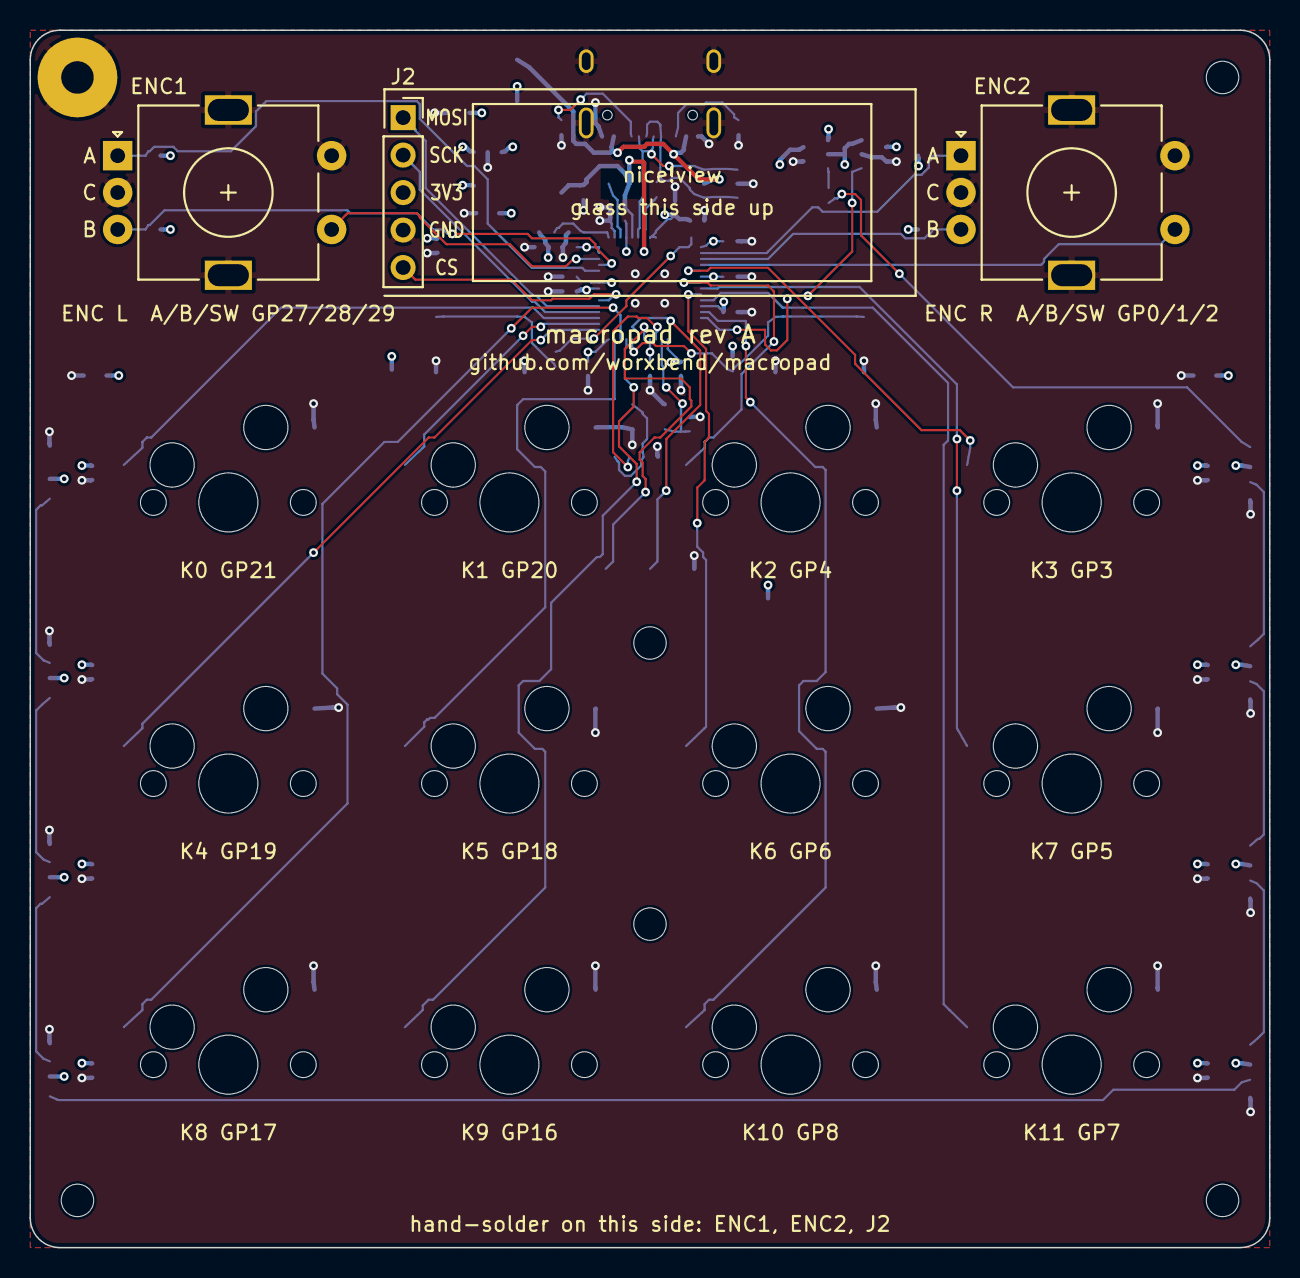
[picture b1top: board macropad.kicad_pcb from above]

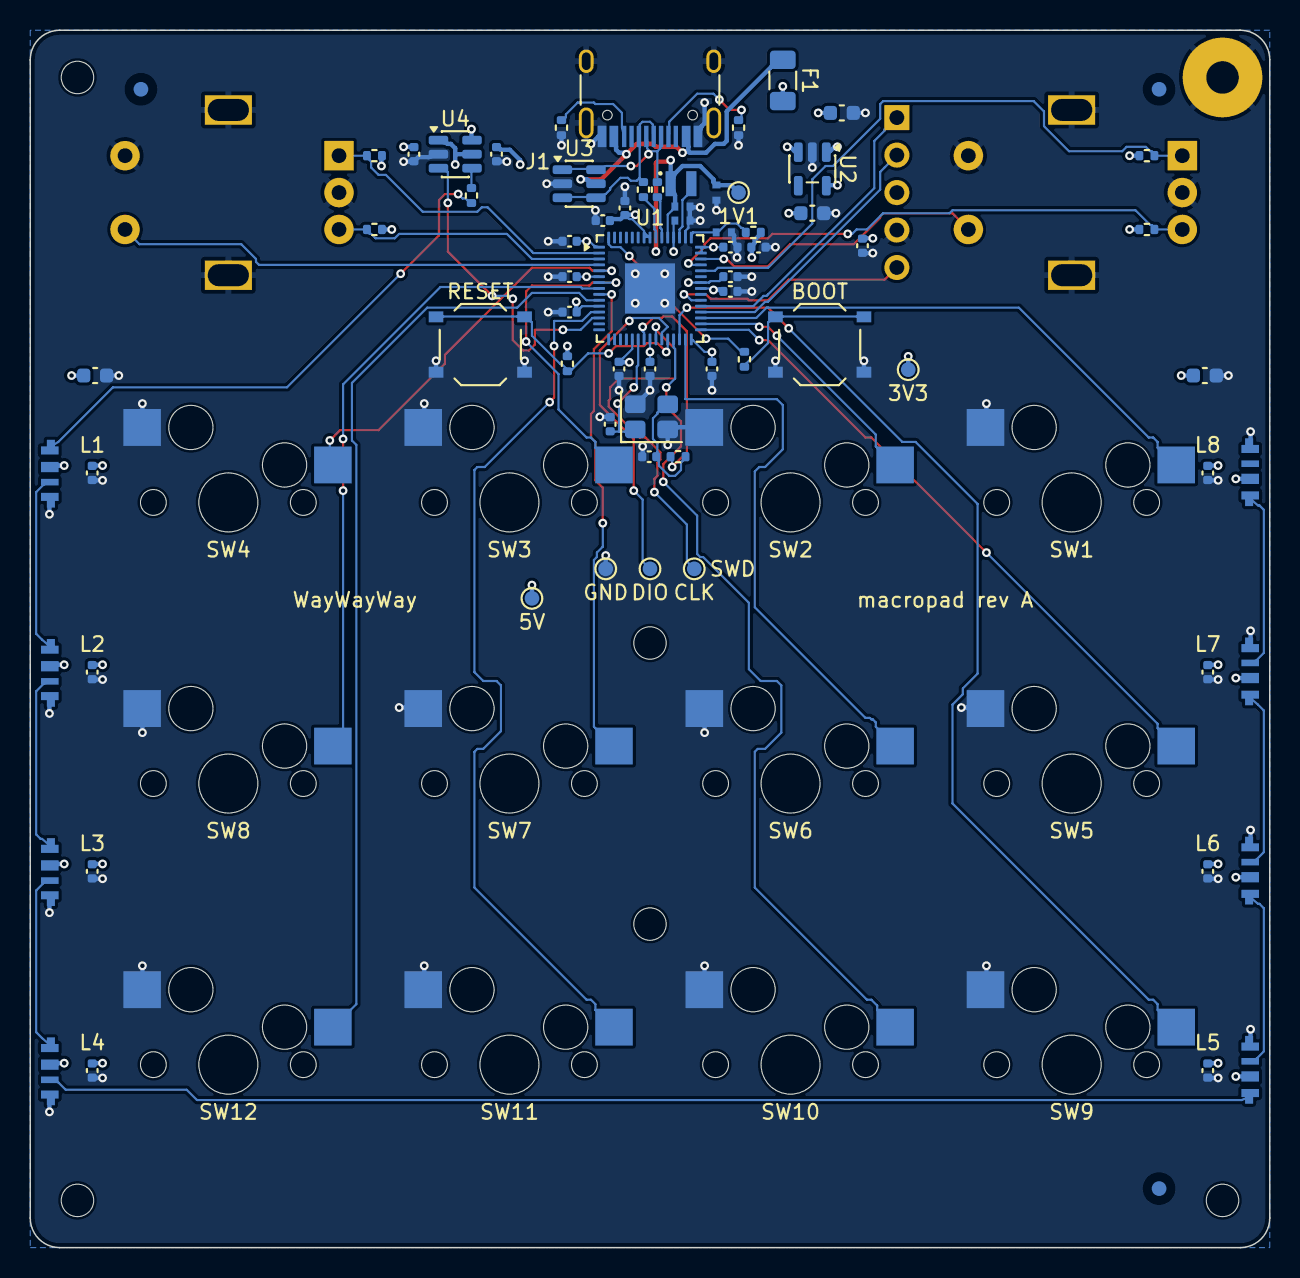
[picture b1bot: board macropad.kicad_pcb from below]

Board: 4 copper layers, 84.0 x 82.5 mm, 94 parts (85 on the bottom side), 52 nets.

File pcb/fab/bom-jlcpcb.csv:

Comment,Designator,Footprint,LCSC Part #
100nF,"C1,C2,C3,C4,C6,C7,C8,C9,C10,C32,C33,C20,C21,C24,C25,C26,C27,C28,C29,C30,C31",C_0402_1005Metric,C1525
10k,R3,R_0402_1005Metric,C25744
10uF,C18,C_0603_1608Metric,C19702
12MHz,Y1,Crystal_SMD_3225-4Pin_3.2x2.5mm,C20625731
15pF,"C15,C16",C_0402_1005Metric,C1548
1k,"R2,R4",R_0402_1005Metric,C11702
1uF,C19,C_0402_1005Metric,C52923
2.2uF,"C17,C22,C23",C_0603_1608Metric,C23630
27R,"R7,R8",R_0402_1005Metric,C25100
3.3k,"R10,R11,R12,R13",R_0402_1005Metric,C25890
3.3uH,L1,L_Abracon_AOTA-B201610,C42411119
330R,R9,R_0402_1005Metric,C25104
33R,R1,R_0402_1005Metric,C25105
4.7uF,C5,C_0402_1005Metric,C23733
4.7uF,"C11,C12,C14",C_0402_1005Metric_Wide,C23733
5.1k,"R5,R6",R_0402_1005Metric,C25905
74LVC1T45,U4,SOT-23-6,C168856
AP2112K-3.3,U2,SOT-23-5,C51118
MX hot-swap,"SW1,SW2,SW3,SW4,SW5,SW6,SW7,SW8,SW9,SW10,SW11,SW12",MX_Hotswap,C49352235
RP2354A,U1,QFN-60-1EP_7x7mm_P0.4mm_EP3.4x3.4mm_ViaWindows,C41378174
SK6812SIDE-A,"LED1,LED2,LED3,LED4,LED5,LED6,LED7,LED8",SK6812-side-a,C5378721
TS-1187A,"SW14,SW13",SW_Push_1P1T_XKB_TS-1187A,C318884
USB-C,J1,USB_C_Receptacle_HRO_TYPE-C-31-M-12,C165948
USBLC6-2SC6,U3,SOT-23-6,C7519
nSMD050,F1,Fuse_1206_3216Metric,C69688

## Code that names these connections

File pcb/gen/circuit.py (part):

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        nets[encoder["gpio_b"]] = f"{name}_B"
        nets[encoder["gpio_sw"]] = f"{name}_SW"
    display = spec["display"]
    nets[display["gpio_sck"]] = "DISP_SCK"
    nets[display["gpio_mosi"]] = "DISP_MOSI"
    nets[display["gpio_cs"]] = "DISP_CS"
    nets[spec["leds"]["gpio_data"]] = "LED_DATA_3V3"
    return nets


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INDUCTOR_PADS = {"1": V1, "2": "VREG_LX"}


# Where the regulator parts sit, from VREG_LX (pin 48) outward, in Raspberry Pi's RP2350A Minimal R4 pattern
# mirrored for the bottom face: CIN across VREG_VIN (49) and PGND (47), COUT right behind it with the two
# ground pads side by side, the inductor beyond both. VREG_LX runs between the capacitor pads.
CIN_DISTANCE = 1.15
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# The inductor sits 0.1 mm toward PGND, so its +1V1 pad clears the USB series resistors.
INDUCTOR_SHIFT = -0.1
# CIN and COUT sit 0.2 mm toward PGND: VREG_FB then runs straight up from pin 50 past CIN's 3.3 V pad,
# and USB D- and D+ run straight up from pins 51 and 52 beside it.
CAPACITOR_SHIFT = -0.2


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def _clock_and_reset() -> list[Part]:
    spec = BOARD_SPEC["buttons"]
    return [
        # The crystal sits as close below XIN/XOUT (MCU pins 21 and 22) as the two hot-swap sockets
        # allow. XIN runs down its right side to pad 1, with its load capacitor right there.
        Part("Y1", "12MHz", "XTAL3225", 41.9, 26.2, 0,
             nets={"1": "XIN", "2": GND, "3": "XTAL_DRIVE", "4": GND}),
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        Part("SW14", "TS-1187A", "TACT", spec["reset"]["x"], spec["reset"]["y"], 0,
             nets={"1": "RUN", "2": GND}),
        # Next to the BOOT button, so the long track across the board is the one behind the resistor.
        # Beside pin 60 it blocks the escapes of KEY4, KEY8 and DISP_CS (three tries, see pcb/README.md "R4").
        Part("R4", "1k", "R0402", 35.6, 22.3, 90, nets={"1": "QSPI_SS", "2": "BOOT"}),
        Part("SW13", "TS-1187A", "TACT", spec["boot"]["x"], spec["boot"]["y"], 0,
             nets={"1": "BOOT", "2": GND}),
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
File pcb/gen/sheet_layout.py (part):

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        Wire(V5, ("F1.2", (54, 12))),
        Wire("CC1", ("J1.A5", "R5.1"), label=(25, 16)),
        Wire("CC2", ("J1.B5", "R6.1"), label=(25, 18)),
        Wire("USB_D_N", ("J1.A7", (28, 22), "R7.1"), label=(31, 22)),
        Wire("USB_D_N", ("J1.B7", (28, 24), (28, 22))),
        Wire("USB_D_P", ("J1.A6", (30, 26), "R8.1"), label=(31, 26)),
        Wire("USB_D_P", ("J1.B6", (30, 28), (30, 26))),
    ),
    rails=(Rail(VBUS, (27, 12)), Rail(V5, (54, 12))),
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    wires=(
        Wire(V1, ("L1.1", "C12.1", "C13.1", (36, 12), (44, 12), "TP6.1")),
        Wire(V3, ((8, 32), "R1.2")),
        Wire("VREG_AVDD", ("R1.1", "C14.1", (36, 32)), label=(26, 32)),
    ),
    rails=(Rail(V1, (36, 12)), Rail(V3, (8, 32))),
    flags=(Flag((44, 12)), Flag((36, 32))),
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    "12 MHz crystal", 6, 102, 72, 28,
    places=(Place("Y1", 22, 12), Place("C15", 13, 15), Place("C16", 31, 15), Place("R2", 39, 12, 270)),
    wires=(
        Wire("XIN", ((5, 12), "C15.1", "Y1.1"), label=(5, 12)),
        Wire("XTAL_DRIVE", ("Y1.3", "C16.1", "R2.2"), label=(26, 12)),
    ),
    notes=(Note("Load capacitors are a guess until measured.", 2, 26),),
)
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    places=(Place("R3", 12, 15), Place("SW14", 22, 22), Place("R4", 45, 22, 90), Place("SW13", 58, 22),
            Place("TP1", 76, 14), Place("TP2", 84, 14), Place("TP3", 92, 14)),
    wires=(
        Wire("RUN", ((5, 22), (12, 22), "SW14.1"), label=(5, 22)),
        Wire("RUN", ("R3.2", (12, 22))),
        Wire("BOOT", ("R4.2", "SW13.1"), label=(49, 22)),
    ),
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    wires=(
        Wire(V3, ("U4.1", (24, 12), (14, 12), (14, 26), "U4.5")),
        Wire(V5, ("U4.6", (28, 12), (32, 12))),
        Wire("LED_DATA_3V3", ("U4.3", (12, 22)), label=(12, 22, "left")),
    ),
    rails=(Rail(V3, (24, 12)), Rail(V5, (32, 12))),
    notes=(Note("DIR high: A drives B.", 2, 34),),
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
